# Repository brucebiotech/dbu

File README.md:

# dbu

This project provides details on both the software and hardware for dbu, a cmsis-dap tool used for debugging ARM processors.

The dbu's main role is as a bootstrapping programmer for more complete multi-target development tools such as the [fizzit pulsar](https://github.com/brucebiotech/splice/blob/main/docs/README.md).

Based on [free-dap](https://github.com/ataradov/free-dap), dbu adds the SAML21 as a platform and introducs the capability to connect to multiple target CPU's.  A single SAML21 can support up to 6 target CPUs.

## How to use dbu

dbu is a component added to a target development board. 

```
                   Target development board
                 .-------------------------------------------------------.
                 |                       Debug target CPUs               |
                 |                                                       |          
cmsis-dap       ---.   .------.         cmsis-dap swd ports              |  
hid host        USB|---| DBU  |------+-----+-----+-----+-----+-----.     |   
adapter         ---'   |      |-.    |     |     |     |     |     |     |   
                 |     `------' |    |0    |1    |2    |3    |4    |5    |   
                 |     SWD|     |  .-+-.  -+-.  -+-.  -+-. .-+-. .-+-.   |   
bootstrap       ---.      |     |  |CPU| |CPU| |CPU| |CPU| |CPU| |CPU|   |
programming      --|------'     |  |   | |   | |   | |   | |   | |   |   |
connector       ---'            |  `-+-' `-+-' `-+-' `-+-' `-+-' `-+-'   |
                 |              |    |     |     |     |     |     |     |
                 |              `----+-----+-----+-----+-----+-----'     |
                 |                        "printf" uarts                 |
                 |                                                       |
                 `-------------------------------------------------------'
		
```
To use dbu, add a SAML21 CPU and a USB connector to your development board and provide a method of bootstrapping the dbu firmware into the SAML21. (This repository includes a low-cost edge connector based adaptor as a [bootstrap option](https://github.com/brucebiotech/dbu/blob/main/hardware/README.md#dbu-bootstrap).)

## Additional features

The dbu software also implements a cmsis-dap vendor extension to control power delivery to the target.

It also supports the cmsis-dap UART commands to tunnel a uart debug message stream over the cmsis-dap HID interface.  In other words dbu enables support for printf debugging of each target CPU over a single USB connection.

## The detail

Follow these links for more information including instructions on building the software and hardware.

[Building the software](https://github.com/brucebiotech/dbu/blob/main/software/README.md)

[Software user guide](https://github.com/brucebiotech/dbu/blob/main/docs/README.md)

[Building the hardware](https://github.com/brucebiotech/dbu/blob/main/hardware/README.md)

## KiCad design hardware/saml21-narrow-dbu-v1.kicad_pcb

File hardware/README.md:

# target hardware

The target hardware is yours to design.  It just needs to incorporate the SAML21 and botstrap programming connector somewhere, e.g as done in the [schematic](https://kicanvas.org/?github=https%3A%2F%2Fgithub.com%2Fbrucebiotech%2Fdbu%2Fblob%2Fmain%2Fhardware%2Fsaml21-narrow-dbu-v1.kicad_sch) and [PCB](https://kicanvas.org/?github=https%3A%2F%2Fgithub.com%2Fbrucebiotech%2Fdbu%2Fblob%2Fmain%2Fhardware%2Fsaml21-narrow-dbu-v1.kicad_pcb) in the hardware folder.

```
                   Your board
                 .-------------------------------------------------------.
                 |                       Your CPUs here...               |
                 |                                                       |          
                ---.   .------.         cmsis-dap                        |  
                USB|---|SAML21|------+-----+-----+-----+-----+-----.     |   
                ---'   |      |-.    |     |                       |     |   
                 |     `------' |    |0    |1         ...          |n    |   
                 |     SWD|     |  .-+-.  -+-.                   .-+-.   |   
                ---.      |     |  |CPU| |CPU|                   |CPU|   |
                 --|------'     |  |   | |   |                   |   |   |
                ---'            |  `-+-' `-+-'                   `-+-'   |
                 |              |    |     |                       |     |
                 |              `----+-----+-----+-----+-----+-----'     |
                 |                             uarts                     |
                 `-------------------------------------------------------'
```
# dbu bootstrap

An option would be to put a standard 10-way debug pin header on the target board.  

As this connector is not used in the normal development workflow of the target, this is an example hardware for bootstrapping that saves the cost and real estate of adding the 10-pin header. 

The bootstrap dbu is connected to a traget using an edge connector on the target's PCB. The particular details of this connection are detailed as J4 on the KiCad [schematic](https://kicanvas.org/?github=https%3A%2F%2Fgithub.com%2Fbrucebiotech%2Fdbu%2Fblob%2Fmain%2Fhardware%2Fsaml21-narrow-dbu-v1.kicad_sch) and [PCB](https://kicanvas.org/?github=https%3A%2F%2Fgithub.com%2Fbrucebiotech%2Fdbu%2Fblob%2Fmain%2Fhardware%2Fsaml21-narrow-dbu-v1.kicad_pcb) hardware files.

You then need a second, bootstrap dbu to attach to the dbu on the target, e.g.

Note that this board has a break-away section for the AVX edge connector. Usually you would detach this section and connect the two parts with the 10-pin right angle pin header.

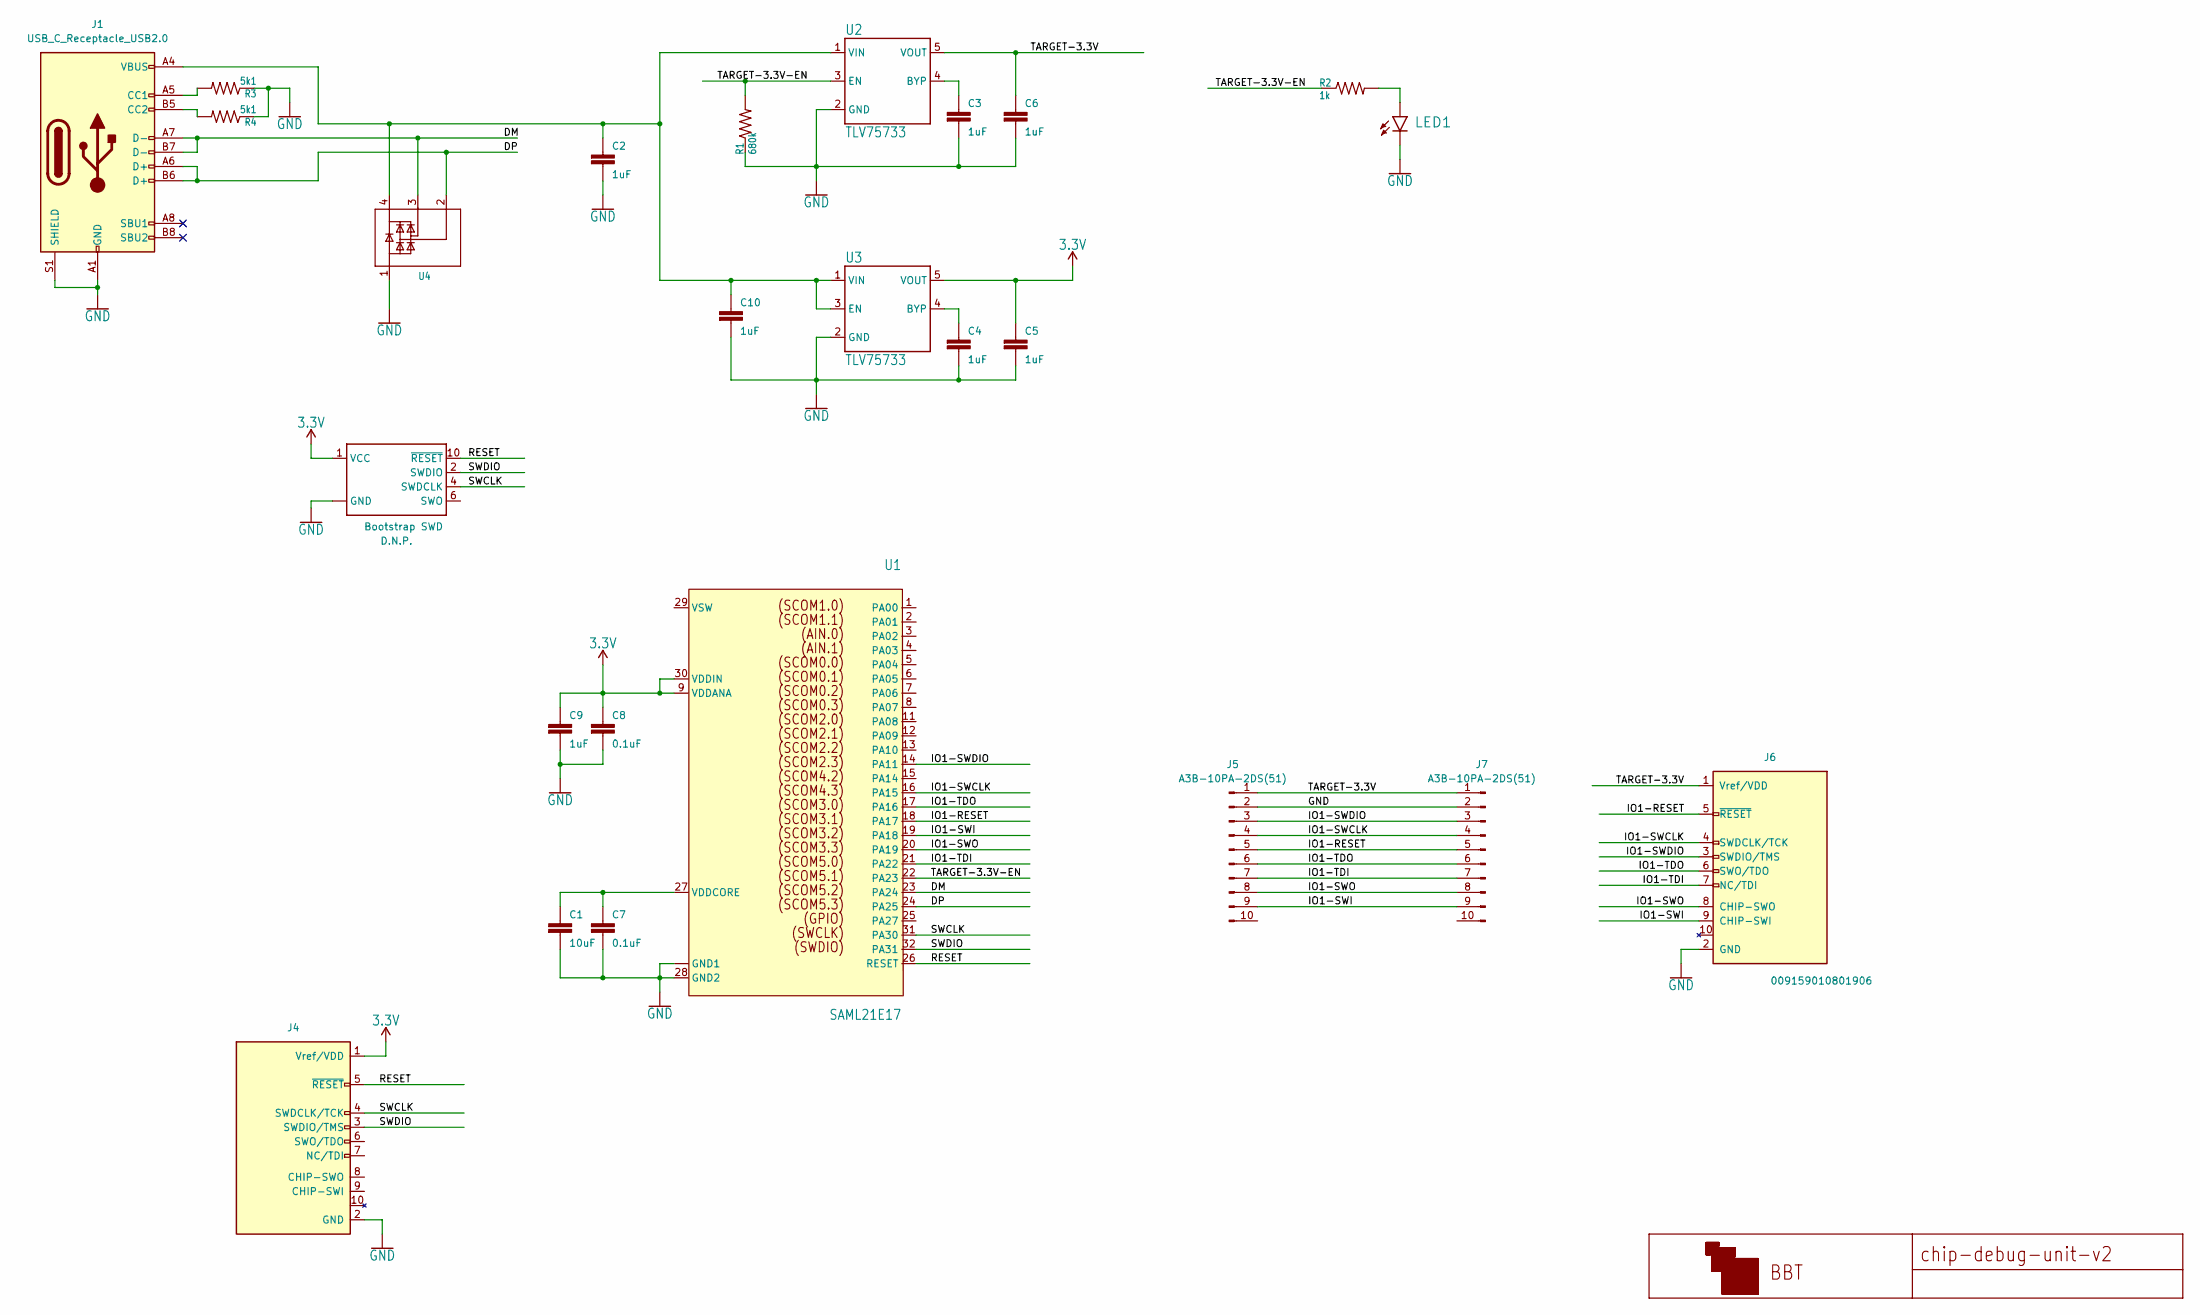
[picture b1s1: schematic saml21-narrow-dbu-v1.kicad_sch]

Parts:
C1: 10uF; 0402
C2, C3, C4, C5, C6, C9, C10: 1uF; 0402
C7, C8: 0.1uF; 0402
J1: USB_C_Receptacle_USB2.0; USB_C_Receptacle_GCT_USB4105-xx-A_16P_TopMnt_Horizontal
J2: Bootstrap SWD; 2X5-SMD-UNSHROUDED
J4: SWD-EDGE; blocks-edge-10-plug
J5: A3B-10PA-2DS(51); PinHeader_2x05_P2.00mm_Vertical
J6: 009159010801906; blocks-edge-10-socket; part_number 009159010801906
J7: A3B-10PA-2DS(51); PinHeader_2x05_P2.00mm_Horizontal
LED1: LED_0603_1608Metric_Pad1.05x0.95mm_HandSolder
R1: 680k; 0402
R2: 1k; R_0402_1005Metric_Pad0.72x0.64mm_HandSolder
R3, R4: 5k1; R_0402_1005Metric_Pad0.72x0.64mm_HandSolder
U1: SAML21E17; TQFP32-08
U2, U3: TLV75733; SOT23-5
U4: PRTR5V0U2-S; SOT143B

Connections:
3.3V: C5.1, C8.1, C9.1, J2.1 (VCC), J4.1 (Vref/VDD), U1.9 (VDDANA), U1.30 (VDDIN), U3.5 (VOUT)
/DM: J1.A7 (D-), J1.B7 (D-), U1.23 (PA24), U4.3
/DP: J1.A6 (D+), J1.B6 (D+), U1.24 (PA25), U4.2
/IO1-RESET: J5.5, J6.5 (~RESET), J7.5, U1.18 (PA17)
/IO1-SWCLK: J5.4, J6.4 (SWDCLK/TCK), J7.4, U1.16 (PA15)
/IO1-SWDIO: J5.3, J6.3 (SWDIO/TMS), J7.3, U1.14 (PA11)
/IO1-SWI: J5.9, J6.9 (CHIP-SWI), J7.9, U1.19 (PA18)
/IO1-SWO: J5.8, J6.8 (CHIP-SWO), J7.8, U1.20 (PA19)
/IO1-TDI: J5.7, J6.7 (NC/TDI), J7.7, U1.21 (PA22)
/IO1-TDO: J5.6, J6.6 (SWO/TDO), J7.6, U1.17 (PA16)
/RESET: J2.10 (~RESET), J4.5 (~RESET), U1.26 (RESET)
/SWCLK: J2.4 (SWDCLK), J4.4 (SWDCLK/TCK), U1.31 (PA30)
/SWDIO: J2.2 (SWDIO), J4.3 (SWDIO/TMS), U1.32 (PA31)
/TARGET-3.3V: C6.1, J5.1, J6.1 (Vref/VDD), J7.1, U2.5 (VOUT)
/TARGET-3.3V-EN: R1.2, R2.1, U1.22 (PA23), U2.3 (EN)
GND: C1.2, C2.2, C3.2, C4.2, C5.2, C6.2, C7.2, C8.2, C9.2, C10.2, J1.A1 (GND), J1.A12 (GND), J1.B1 (GND), J1.B12 (GND), J1.S1 (SHIELD), J2.3 (GND), J2.5 (GND), J2.9 (GND), J4.2 (GND), J5.2, J6.2 (GND), J7.2, LED1.C, R1.1, R3.1, R4.1, U1.10 (GND1), U1.28 (GND2), U1.EP (GND1), U2.2 (GND), U3.2 (GND), U4.1
unnamed: J1.A5 (CC1), R3.2
unnamed: J1.B5 (CC2), R4.2
unnamed: LED1.A, R2.2
unnamed: C1.1, C7.1, U1.27 (VDDCORE)
unnamed: C3.1, U2.4 (BYP)
unnamed: C2.1, C10.1, J1.A4 (VBUS), J1.A9 (VBUS), J1.B4 (VBUS), J1.B9 (VBUS), U2.1 (VIN), U3.1 (VIN), U3.3 (EN), U4.4
unnamed: C4.1, U3.4 (BYP)

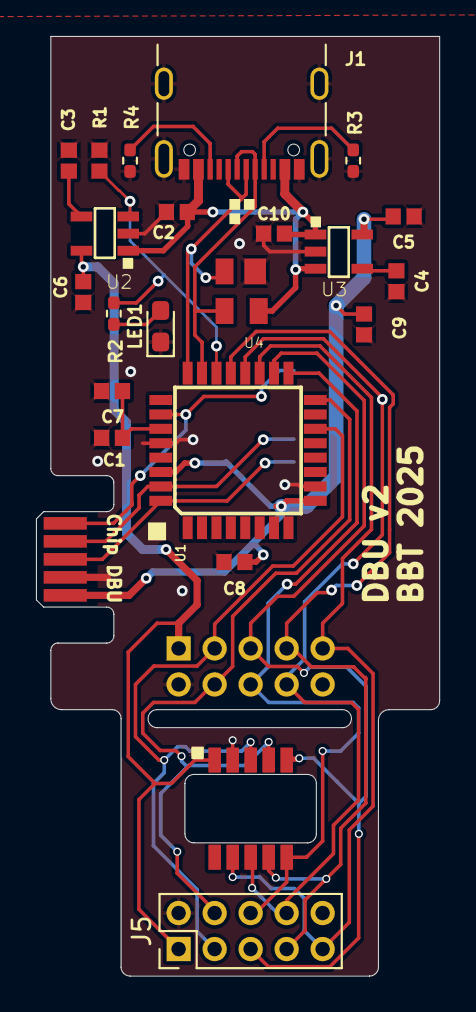
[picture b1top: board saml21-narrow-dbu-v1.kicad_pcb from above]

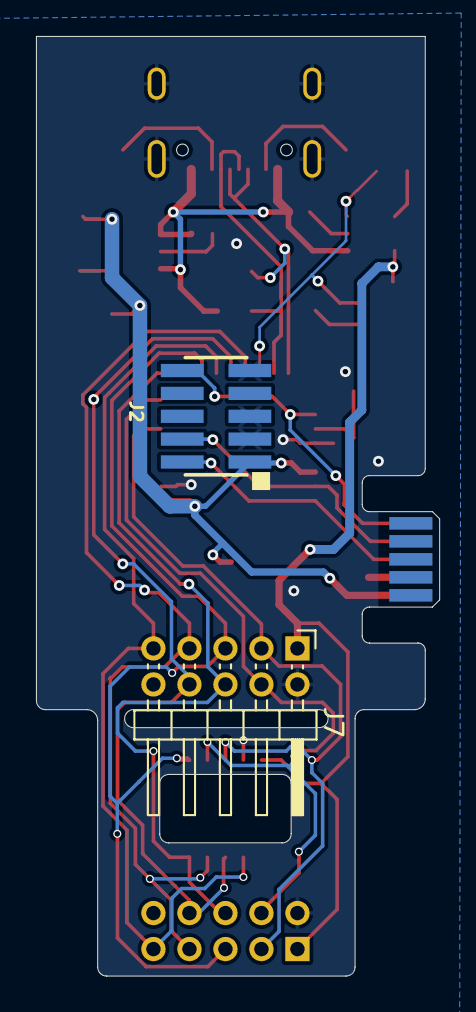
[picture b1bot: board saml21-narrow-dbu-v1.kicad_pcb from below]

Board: 2 copper layers, 22.4 x 52.2 mm, 25 parts (2 on the bottom side), 23 nets.

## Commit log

2025-06-08 Update LICENSE
2025-06-08 initial
2025-06-09 added pcb
2025-06-09 renamed pcb dir
2025-06-09 created docs dir
2025-06-09 created software dir
2025-06-09 change file name
2025-06-09 expand read.me to hardware and software
2025-06-09 clean out old code
2025-06-10 added git ignore
2025-06-10 Create LICENSE
2025-06-10 added printf uarts
2025-06-12 added roadmap
2025-08-14 rename multi debug unit
2025-09-12 fixed pin muxing
2025-11-25 removed unused boards
2025-11-25 added fizzit pulsar board
2025-11-25 added terms of use on the dbu USB vendor ID
2025-11-25 edit terms of use on the dbu USB vendor ID
2025-11-27 added vendor extensions to support ice40 fpga target
